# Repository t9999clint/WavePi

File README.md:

# WavePi
## Multifuntion synth platform for Raspberry Pi and other single board computers.

### Project page... https://www.retroimperfections.com/wavepi/

### Discussion Forum... https://www.vogons.org/viewtopic.php?f=62&t=65908

WavePi aims to be a Open Source, all in one synth solution for older PCs that lack the grunt to use modern synthesizer software.

Meant mainly to be a drop-in replacement for a Waveblaster daughterboard for a SoundBlaster card for the 90’s, however it can also be configured for several different uses. You can connect to any Midi port, or even through serial to the host machine.
This device can also act as a standalone synth in a professional music stack. Plug it into a Midi Keyboard or Guitar and use it to rock out!

I use it to play old games on my MS-DOS pc with improved music, but I also built one for my Mom to practice piano with on a old 90’s Yamaha Midi keyboard I found at goodwill. (My synth sounds far more realistic than the built in synth)
I decided to keep the project 100% open source in hopes that this project will continue on long after I am no longer able to work on it.

The components required for this are simple.
1. Small computer running Linux (preferably debian). 1gb ram or greater is strongly recommended for best results.
2. Midi interface of some kind (USB, Serial, etc…)
3. DAC of some kind to pump out the audio with
4. Something to send it Midi data with (MS-DOS games, Midi Instrument, etc…)

The hardware I am developing this project with is as follows…
1. Raspberry Pi 3B+ running Raspbian.
2. Serial 2 Midi interface wired into Waveblaster header on MS-DOS PC
3. USB DAC plugged into the Ras Pi
4. Intel 486 DX2 PC running MS-DOS 6.22 and a Soundblaster 16 with the Rasp Pi wired into it for Midi Data and power.

I will be making a rasbian image for the ras pi 3, but I want to add a few more features first.

### The installation instructions are as follows, keep in mind that the project is in beta state right now.
1. Install debian based os on your synth device. For Raspberry Pi's I strongly recommend raspbian lite (no gui = more ram)
2. (OPTIONAL) I highly recommend enabling openssh-server so you can remotly manage the files and whatnot using putty and filezilla -- **sudo apt install openssh-server -yy && sudo systemctl enable ssh**
3. (OPTIONAL)update rasbian to latest firmware and whatnot. -- **sudo rpi-update**
4. Update other packages -- **sudo apt update && sudo apt upgrade -yy && reboot**
5. configure audio levels -- **alsamixer**
6. (optional, but **_STRONGLY_** recommended) change default password for pi user. -- **passwd**
7. Use wget to download latest WavePi release -- **wget https://github.com/t9999clint/WavePi/archive/v0.9.0.tar.gz**
8. use tar to extract the archive -- **tar xzf v0.9.0.tar.gz**
9. rename extracted folder to WavePi -- **mv WavePi-0.9.0 WavePi** 
10. change to WavePi directory -- **cd WavePi**
11. make it executable -- **chmod +x ./install.sh**
12. run install-munt.sh as root to compile and install munt to your system. Go get some coffee this will take a bit. -- **sudo ./install.sh**
13. copy over soundfonts and munt rom files to appropriate folders using filezilla or something.
14. change to the configs subfolder -- **cd ../configs**
15. use aplay to get your alsa device number. -- **aplay -l**
16. edit main.cfg file and modify the device numbers to match your hardware -- **nano main.cfg**
17. edit the 000.cfg and modify the soundfont settings to match the soundfont you downloaded. -- **nano 000.cfg**
18. (optional) create more config files by copying the 000.cfg and configure them for other soundfonts. -- **cp 000.cfg 003.cfg**
19. reboot -- **sudo reboot**

Now there are two ways to control WavePi, either by using the wavepi command, or by sending it special sysex messages.

## WavePi command syntax
- **wavepi 000 :**
   By entering in a 3 digit number it will attempt to load a config file matching that number in the sonfigs folder. if no file is found it will attempt to load the default config instead (usually 000.cfg).
- **wavepi configfile.cfg :**
   By entering a config file, must have .cfg as an extention and contain no spaces in it's filepath/name, wavepi will load that instead of using a numbered config in the config folder.
- **wavepi soundfont.sf2 :**
   By entering a .sf2 file, wavepi will start it up using the soundfont.sh script. (all files cannot contain spaces in it's name or folder path)
- **wavepi stop :**
   By entering this command, wavepi will check what synth is currently running and stop it using the pkill -P PID command. (please note that the script is smart enough to only allow one synth to run at a time, if you start a synth while one is already running, it'll stop the currently running one first)
  
## WavePi Sysex messages.
- These messages are using the same format as the ones that Falcosoft MidiPlayer uses. **F0 66 04 00 F7** is for config 000, **F0 66 04 09 F7** is for config 009 (there is currently a bug that limits this to only 000-009)
- This can be sent from MS-DOS using this script... https://downloads.kor.ninja/Music/wavepi/sysex.zip

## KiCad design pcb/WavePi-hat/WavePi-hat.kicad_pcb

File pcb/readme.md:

# KiCad Files go here.

BOM will go here eventually...

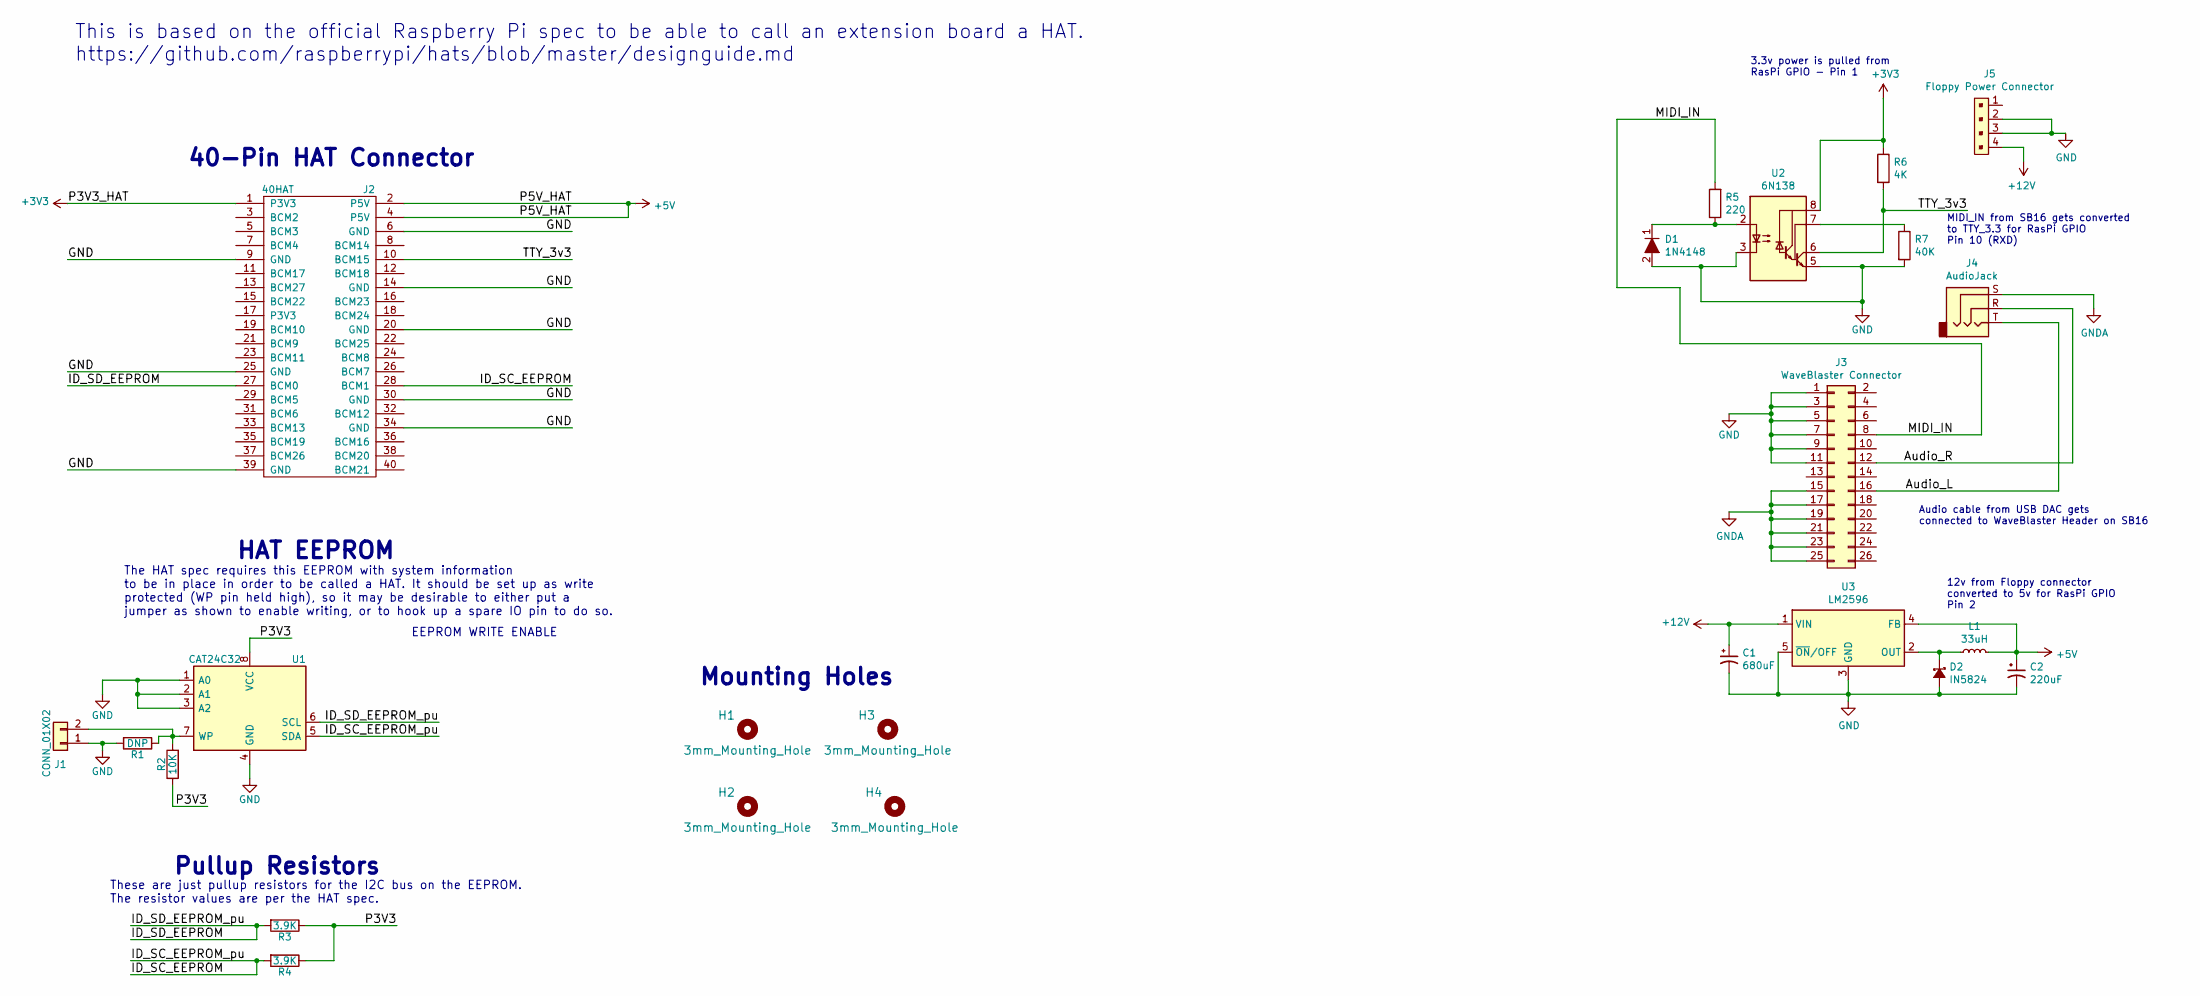
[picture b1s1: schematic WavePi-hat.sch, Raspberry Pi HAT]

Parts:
C1: 680uF; CP_Radial_D5.0mm_P2.00mm
C2: 220uF; CP_Radial_D5.0mm_P2.00mm
D1: 1N4148; D_A-405_P10.16mm_Horizontal; MPN 1N4148; Digi-Key_PN 1N4148FS-ND
D2: IN5824; D_A-405_P10.16mm_Horizontal
H1, H2, H3, H4: 3mm_Mounting_Hole; NPTH_3mm_ID
J1: CONN_01X02; PinHeader_1x02_P2.54mm_Vertical
J2: 40HAT; PinSocket_2x20_P2.54mm_Vertical
J3: WaveBlaster Connector; PinSocket_2x13_P2.54mm_Vertical
J4: AudioJack; Jack_3.5mm_CUI_SJ1-3533NG_Horizontal_CircularHoles
J5: Floppy Power Connector; PinHeader_1x4_P2.54mm_Drill1.02mm; MPN 0022232041; Digi-Key_PN WM4202-ND
L1: 33uH; L_Radial_L8.0mm_W8.0mm_P5.00mm_Neosid_SD8
R1: DNP; R_0603_1608Metric
R2: 10K; R_0603_1608Metric
R3, R4: 3.9K; R_0603_1608Metric
R5: 220; R_Axial_DIN0204_L3.6mm_D1.6mm_P7.62mm_Horizontal
R6: 4K; R_Axial_DIN0204_L3.6mm_D1.6mm_P7.62mm_Horizontal
R7: 40K; R_Axial_DIN0204_L3.6mm_D1.6mm_P7.62mm_Horizontal
U1: CAT24C32; SOIC-8_3.9x4.9mm_P1.27mm
U2: 6N138; DIP-8_W10.16mm
U3: LM2596; TO-263-5_TabPin3

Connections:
+3V3: J2.1 (P3V3), R6.1, U2.8 (VCC)
+5V: C2.1, J2.2 (P5V), J2.4 (P5V), L1.2, U3.4 (FB)
+12V: C1.1, J5.4, U3.1 (VIN)
/Audio_L: J3.16, J4.T
/Audio_R: J3.12, J4.R
/ID_SC_EEPROM: J2.28 (BCM1), R4.2, U1.5 (SDA)
/ID_SD_EEPROM: J2.27 (BCM0), R3.2, U1.6 (SCL)
/MIDI_IN: J3.8, R5.2
/P3V3: R2.1, R3.1, R4.1, U1.8 (VCC)
/TTY_3v3: J2.10 (BCM15), R6.2, U2.6 (VO2)
GND: C1.2, C2.2, D1.2, D2.2 (A), J1.1, J2.6 (GND), J2.9 (GND), J2.14 (GND), J2.20 (GND), J2.25 (GND), J2.30 (GND), J2.34 (GND), J2.39 (GND), J3.1, J3.3, J3.5, J3.7, J3.9, J3.11, J5.2, J5.3, R1.2, R7.2, U1.1 (A0), U1.2 (A1), U1.3 (A2), U1.4 (GND), U2.3 (C2), U2.5 (GND), U3.3 (GND), U3.5 (~ON~/OFF)
GNDA: J3.15, J3.17, J3.19, J3.21, J3.23, J3.25, J4.S
unnamed: D1.1, R5.1, U2.2 (C1)
unnamed: D2.1 (K), L1.1, U3.2 (OUT)
unnamed: J1.2, R1.1, R2.2, U1.7 (WP)
unnamed: R7.1, U2.7 (VO1)

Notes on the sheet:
EEPROM WRITE ENABLE
Pullup Resistors
HAT EEPROM
Mounting Holes
40-Pin HAT Connector
The HAT spec requires this EEPROM with system information to be in place in order to be called a HAT. It should be set up as write protected (WP pin held high), so it may be desirable to either put a jumper as shown to enable writing, or to hook up a spare IO pin to do so.
These are just pullup resistors for the I2C bus on the EEPROM. The resistor values are per the HAT spec.
This is based on the official Raspberry Pi spec to be able to call an extension board a HAT. https://github.com/raspberrypi/hats/blob/master/designguide.md
12v from Floppy connector converted to 5v for RasPi GPIO Pin 2
Audio cable from USB DAC gets connected to WaveBlaster Header on SB16
MIDI_IN from SB16 gets converted to TTY_3.3 for RasPi GPIO Pin 10 (RXD)
3.3v power is pulled from RasPi GPIO - Pin 1

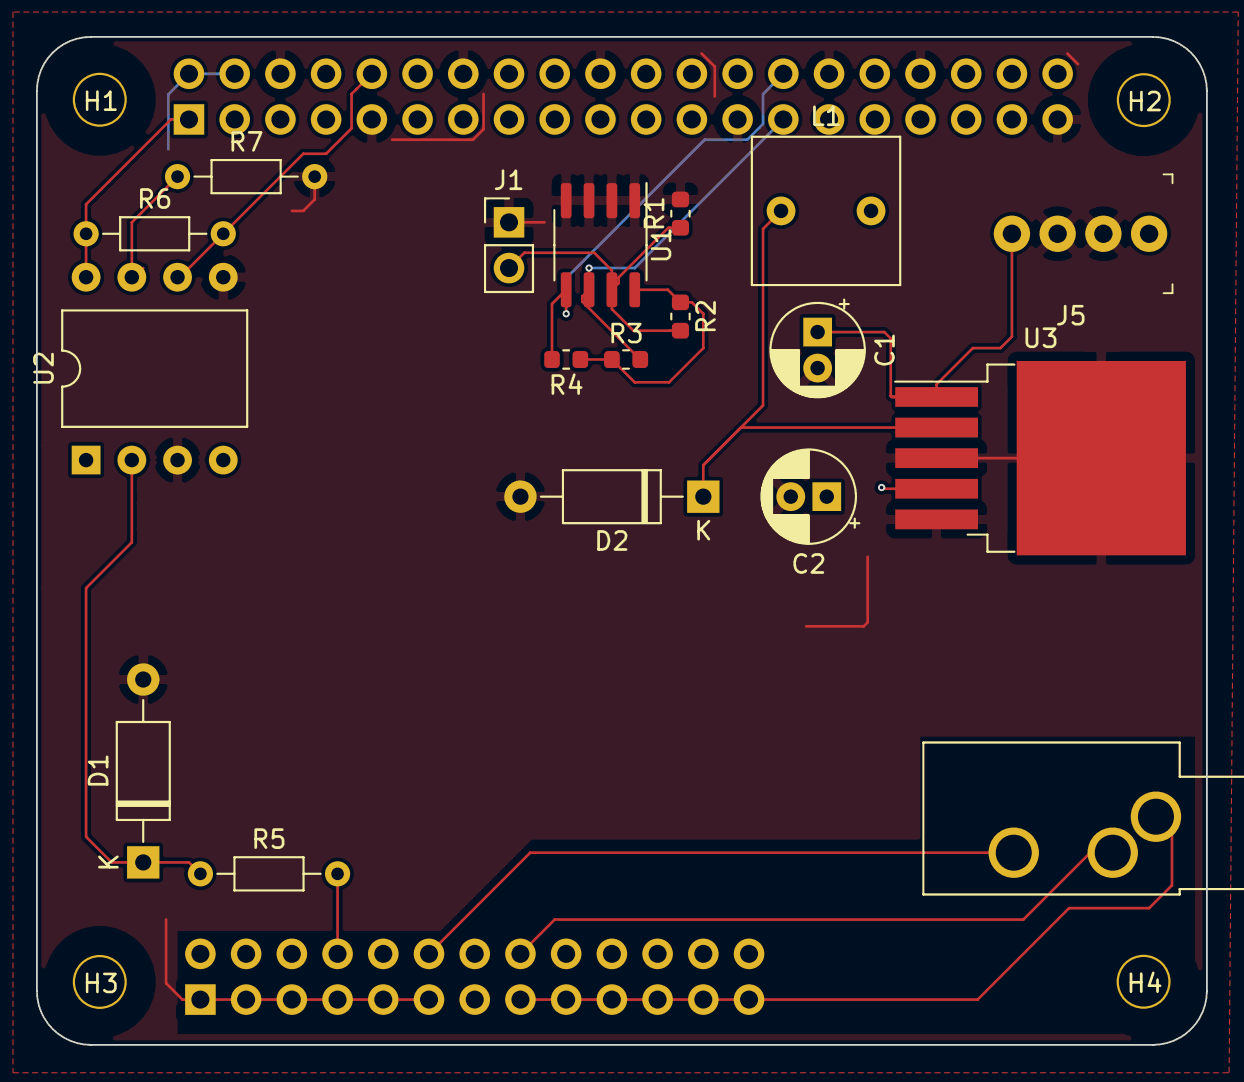
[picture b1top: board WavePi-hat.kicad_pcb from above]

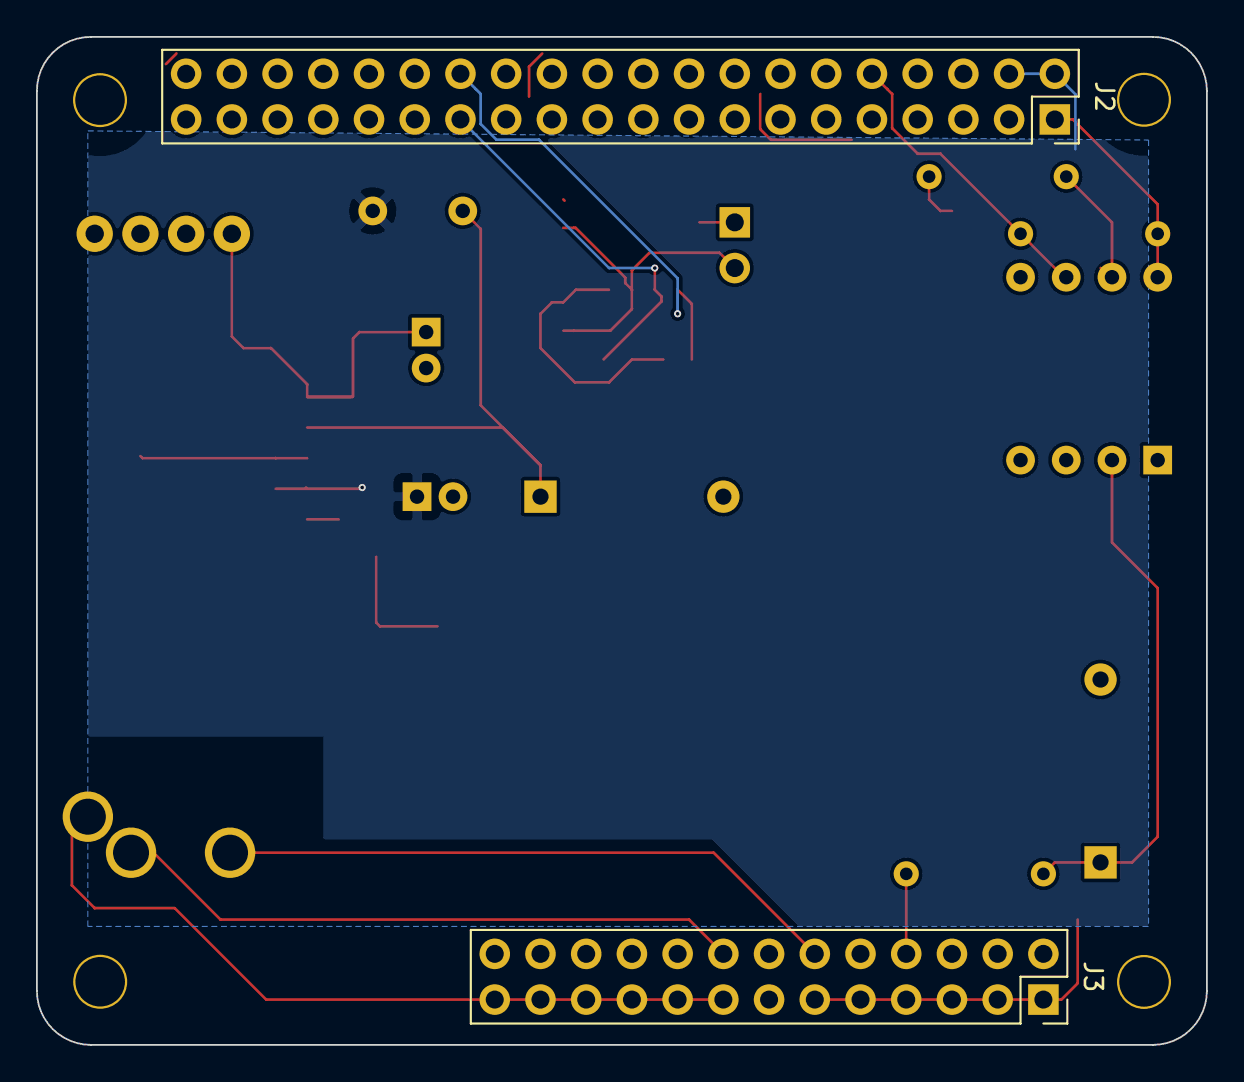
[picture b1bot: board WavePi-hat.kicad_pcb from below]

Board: 4 copper layers, 65.0 x 56.0 mm, 24 parts (2 on the bottom side), 16 nets.

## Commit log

2019-06-18 Create Notes for hue_plus
2019-06-18 Rename Notes for hue_plus to Notes for hue_plus.txt
2019-06-18 making initial file structure...
2019-06-18 Rename fluidsynth.sh to scripts/fluidsynth.sh
2019-06-18 Updated instructions to be multithreaded
2019-06-23 Added manual profile switching functionality
    Script will now autostop previously running config, not cleanly though, but that'll be fixed later.
2019-06-25 made the config file more descriptive
    made the config file more descriptive and also added the WAVEPI_USER option
2019-06-25 Update and rename startconfig.sh to wavepi.sh
    since this file has ballooned into doing basically everything now, I decided to just rename it to wavepi.sh
    I also added the stop command option, basically making it feature complete now. (yay)
    only minor stuff should be changed on this file now... especially when I start making this project more public.
2019-06-25 Added better description
2019-06-25 fixed it so it actually works
2019-06-25 Create wavepi-service.conf
    this should make installing as a service easier
2019-06-25 made script to install wavepi as a service
2019-06-25 ugly first draft
    just to get things running. it only can switch from configs 0-9. rtmidi seems to truncate the other digits...
2019-06-26 Rename fluidsynth.sh to soundfont.sh
2019-06-26 Added proper logging and sf2 loading without a cfg
    Added soundfont loading without a config. looks like I found a bug though... I'm not sure how to fix it so I'll leave it there for now.
    It wont load any files with spaces in them...
2019-06-26 Update and rename Notes for mt32emu.txt to install-munt.sh
    changed the notes to a script. Just to make things easier...
2019-06-26 Added basic tutorial...
2019-06-26 fixed formating issues
2019-06-26 fixing more formatting
2019-06-27 Update README.md
    added download url
2019-07-05 Uploading basic draft of WaveBlaster adapter
    Just a basic draft, there are a number of mistakes, not sure if it'll even work yet.
    Hopefully this will work as a good starting point.
2019-07-07 Fixing errors in install script
2019-07-07 fixing python issues
2019-07-07 relative paths not working.
2019-07-07 changing to make things obvious
    changed the default so the lcd script will display a missing config error if the synth hasn't been run yet
2019-07-07 fix for rtmidi issues
    added a workaround for odd rtmidi behavior
2019-07-07 updated install instructions
    updated instructions for auto-generated wavepi release file.
2019-07-07 added better cpu compatibility
    made the script aware of the max cores in a system and made it act accordingly.
    also fixed the wrong command being used for press a key prompt. (I'm too used to MS-DOS)
2019-07-23 Fixed instructions so they actually work
    there were a number of minor mistakes in the tutorial. I ran this through some more testing to see if it's working on a fresh install of raspbian, It seems to work fine now.
2019-07-23 Changed default to Pro7use
    Changed the default to pro7 so that I can make things easier for low powered devices. Also quicker loading.
2019-07-23 fixing a typo
2019-07-23 downloads default soundfont.
    Soundfont is not GPL friendly yet, so I don't want to host it up here.
2019-07-23 fixing wrong directory entered
2019-07-23 fixing typo
2019-07-24 adding ttymidi support
2019-07-25 Add support for TTYMidi
    adding support for MIDI over Serial.
    My prototype was successful and therefore it's time to get this implemented in software.
2019-07-25 Add ttymidi support
    Added a rough implementation of ttymidi support. Still need a cleaner way to connect to ttymidi and cleaner way to shut it down.
2019-09-09 Updated ttymidi to version with SysEx support
2019-09-10 Tweaked ttymidi a little bit. Reworked midi-listen.py to support LCDs. Modified some scripts in order to support LCDs.
2019-10-03 Removed SYNTH_LCD_NAME. Updated script to use RUNNING_SYNTH_NAME instead. Modified SYNTH_NAME of configs so it fits on the LCD.
2019-10-03 Reverted standard settings
2019-10-03 Chosen synth configuration will now be updated on the LCD. Implemented ability to change synth configuration via SysEx message back.
2019-10-03 Bugfix for SysEx LCD messages regarding whitespaces.
2019-10-14 new default for LCD screen
    making new default message
2019-10-14 Autodetect Pi revision
    adding some code to test to autodetect the hardware automatically and compile accordingly.
2019-10-14 renamed to install.sh
    this will install everything cept for the hue-plus stuff
2019-10-14 DietPi is new target OS platform
    changing the default settings to work better with the DietPi installation script
2019-10-14 Fixed Autodetection
    Basic tests seem to be working.
    Next steps I wan to do is maybe to integrate the other installation scripts into this one.
2019-10-14 change to target dietpi as default os
2019-10-14 Adding MT-32 config
2019-10-14 renaming to CM32L
2019-10-15 Updated for LCD code
2019-10-15 More changes for LCD code
2019-10-15 Adding support for DietPi
    these are some autoconfig files that I will be using for the distro release.
    Just a first draft
2019-10-15 Update dietpi.txt
    just some more testing
2019-10-15 New install process
    We are now in Beta
2019-10-17 slight modification to script
    still haven't tested this yet, but it should work better this time. I still need to change the internet delay after the setup is done, but I'm not sure how to do that yet.
2019-10-17 Tweaked the optimizations.
    Not sure if this works yet, This will require more testing before I put it in a release.
2019-10-17 export env var as root
    possible solution to performance issues?
2019-10-17 Fixing permission and sudo issues
    This should make a difference now
2019-10-17 Fixing permission issues
2019-10-17 added a line for debug only
2019-10-17 added another line for debug
2019-10-18 fixing auto install issues
2019-10-18 fixing auto install bugs
2019-10-18 Simplifying things
2019-10-18 Changing to match new release version
2019-10-18 changing to match new version
2019-10-18 Fixed installation bugs
    Tested this one a few times and it seems to work...
    Not entirely sure why
2019-10-18 fixed typo
2019-10-18 fixing wrong directory name on cleanup
2019-10-18 fix for prompt durring jack2 install
    this should help the automation process
2019-10-18 changing default sound device to the onboard
    not sure how helpful this is, but I'll keep it in for now.
2019-10-19 implementing workaround for memory issues
2019-10-19 Re-enabled workarounds for ram issue
    and so the uglyhacks are back in play
2019-10-21 aconnect cleanup
    hopefully this will solve some of the weird note bugs I've noticed...
2019-10-21 fixing aconnect script
2019-10-21 LCD text update
2019-10-21 Undoing last change
    grep doesn't like spaces
2019-10-21 Fixing aconnect bug
2019-10-21 Disabling uglyhack for aconnect
    lets hope it's working now.
2019-10-24 Combining install scripts
    combining install scripts and adding updated fluidsynth to the compile.
2019-10-24 updated for permissions
2019-10-24 No longer needed
    This has been integrated with the main install script now
2019-10-24 Updating for next release
2019-10-24 Just a simple autoconfig script for testing
    replace the default autoconfig script with this one and it'll always compile the latest testing version (hopefully)
2019-10-24 added git install
2019-10-24 added ldconfig
2019-10-24 fixing string formating typos
2019-10-24 updated instructions for new release
2019-11-15 changing priorities for ttymidi
    bug hunting for serial support
2019-11-16 fix bug for 009 config limit
    the new limit for the configs should be 000-127
2019-11-16 wouldn't launch ttymidi
    it launches ttymidi as root. this is just until I figure out why it won't run as wavepi
2019-12-21 Uploading 3d print files
2019-12-21 wrong filename
2019-12-21 Uploading 3D Design files
    this time with the proper names
